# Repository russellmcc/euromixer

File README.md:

Here's a simple design for a mixing utility eurorack module.

This work is copyright 2013 by Russell McClellan and Brendan Powers, licensed under a [Creative Commons Attribution-ShareAlike 3.0 Unported License.](http://creativecommons.org/licenses/by-sa/3.0/deed.en_US)

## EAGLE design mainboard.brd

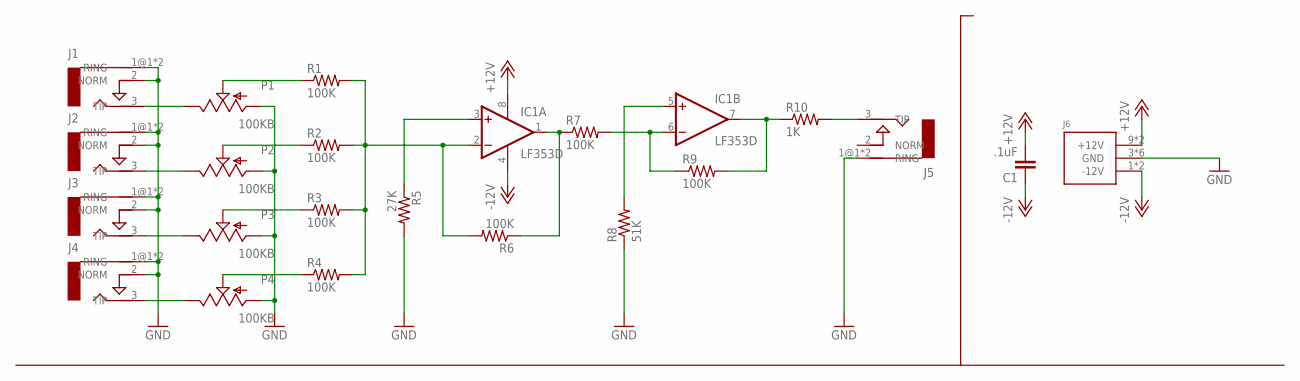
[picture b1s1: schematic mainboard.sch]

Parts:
C1: .1uF; 0603-CAP
IC1: LF353D; SO08
J1, J2, J3, J4, J5: AUDIO-JACKERTHENVAR; ERTHENVAR-JACK
J6: POWER_SIMPLE16; POWER_16
P1, P2, P3, P4: 100KB; PDB12
R1, R2, R3, R4, R6, R7, R9: 100K; 0603-RES
R5: 27K; 0603-RES
R8: 51K; 0603-RES
R10: 1K; 0603-RES

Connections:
+12V: C1.2, IC1.8 (V+), J6.9 (+12V), J6.10 (+12V)
-12V: C1.1, IC1.4 (V-), J6.1 (-12V), J6.2 (-12V)
GND: J1.1@1 (RING), J1.1@2 (RING), J1.2 (NORM), J2.1@1 (RING), J2.1@2 (RING), J2.2 (NORM), J3.1@1 (RING), J3.1@2 (RING), J3.2 (NORM), J4.1@1 (RING), J4.1@2 (RING), J4.2 (NORM), J5.1@1 (RING), J5.1@2 (RING), J6.3 (GND), J6.4 (GND), J6.5 (GND), J6.6 (GND), J6.7 (GND), J6.8 (GND), P1.1 (A), P2.1 (A), P3.1 (A), P4.1 (A), R5.2, R8.1
J1: J1.3 (TIP), P1.3 (E)
unnamed: J3.3 (TIP), P3.3 (E)
unnamed: J2.3 (TIP), P2.3 (E)
unnamed: J5.3 (TIP), R10.2
unnamed: P1.2 (S), R1.1
unnamed: P2.2 (S), R2.1
unnamed: J4.3 (TIP), P4.3 (E)
unnamed: P3.2 (S), R3.1
unnamed: IC1.1 (OUT), R6.1, R7.1
unnamed: IC1.3 (+IN), R5.1
unnamed: P4.2 (S), R4.1
unnamed: IC1.2 (-IN), R1.2, R2.2, R3.2, R4.2, R6.2
unnamed: IC1.7 (OUT), R9.2, R10.1
unnamed: IC1.6 (-IN), R7.2, R9.1
unnamed: IC1.5 (+IN), R8.2

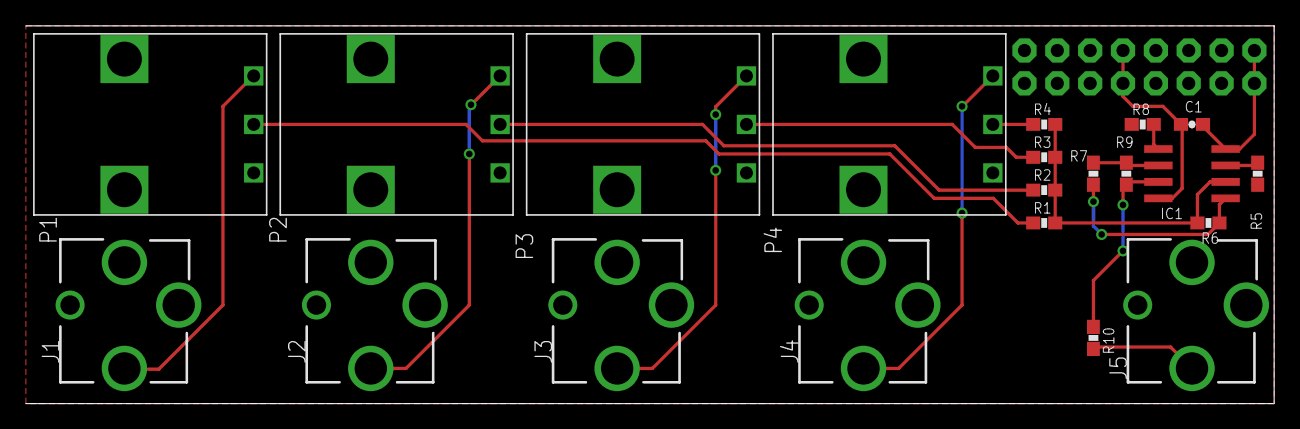
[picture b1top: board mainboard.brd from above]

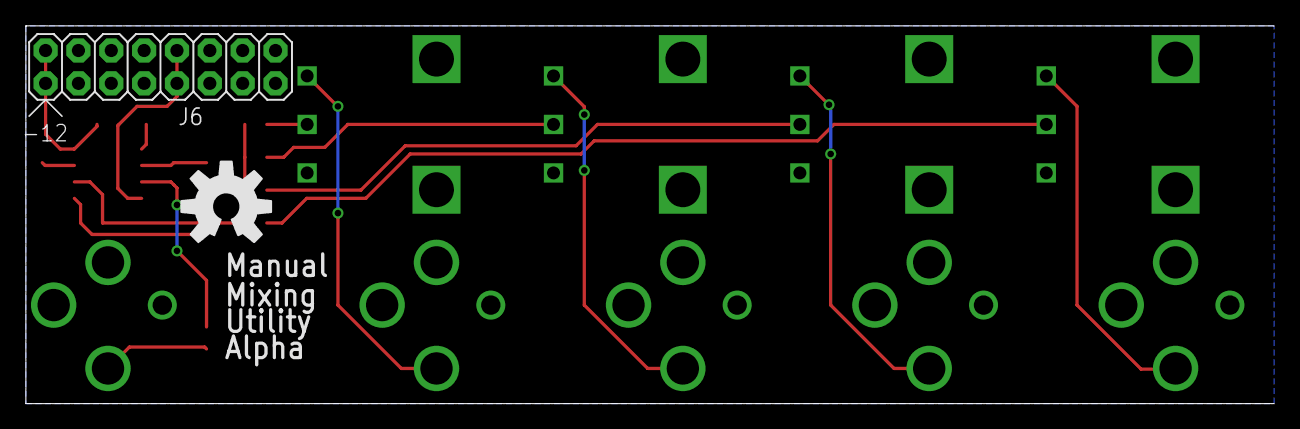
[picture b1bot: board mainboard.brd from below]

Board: 2 copper layers, 96.5 x 29.2 mm, 23 parts (2 on the bottom side), 18 nets.

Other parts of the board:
U$1: OSHW-LOGO-L

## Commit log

2013-07-30 initial
2013-07-30 added bom
2013-07-30 Switched to 16 pin connector.
2013-07-30 added gitignore
2013-08-05 @brendan0powers helped me fix the schem/board
2013-08-05 added Brendan to copyright notice
2013-08-06 added mouser link
2013-08-10 fix for silkscreen
2013-09-16 added frontpanel EPS, corrected silkscreen.
2013-09-16 it's now tested.

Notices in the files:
parts and their libraries:
SparkFun: Licensing: CC v3.0 Share-Alike You are welcome to use this library for commercial purposes.
